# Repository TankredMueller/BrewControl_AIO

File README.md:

# BrewControl_AIO
A top hat rail implementation of the world famous AiO brew control.

For further information on AiO brewControl, see http://hobbybrauer.de/forum/wiki/doku.php/brauen_mit_arduino_all_in_one_aio

This project consists of the following parts:
- A PCB design suitable to be integrated in a top hat rail case
  -> for a preconfigured shopping cart, please use this link: https://www.reichelt.de/my/1339621
- A wiring plan (see https://github.com/TankredMueller/BrewControl_AIO/blob/master/AIO_project_wiring_plan.pdf)

Please note that this project is still in early beta status! You are welcome to build it, but don´t take it personally if something goes wrong. I will assume no responsibility for any use of this project.

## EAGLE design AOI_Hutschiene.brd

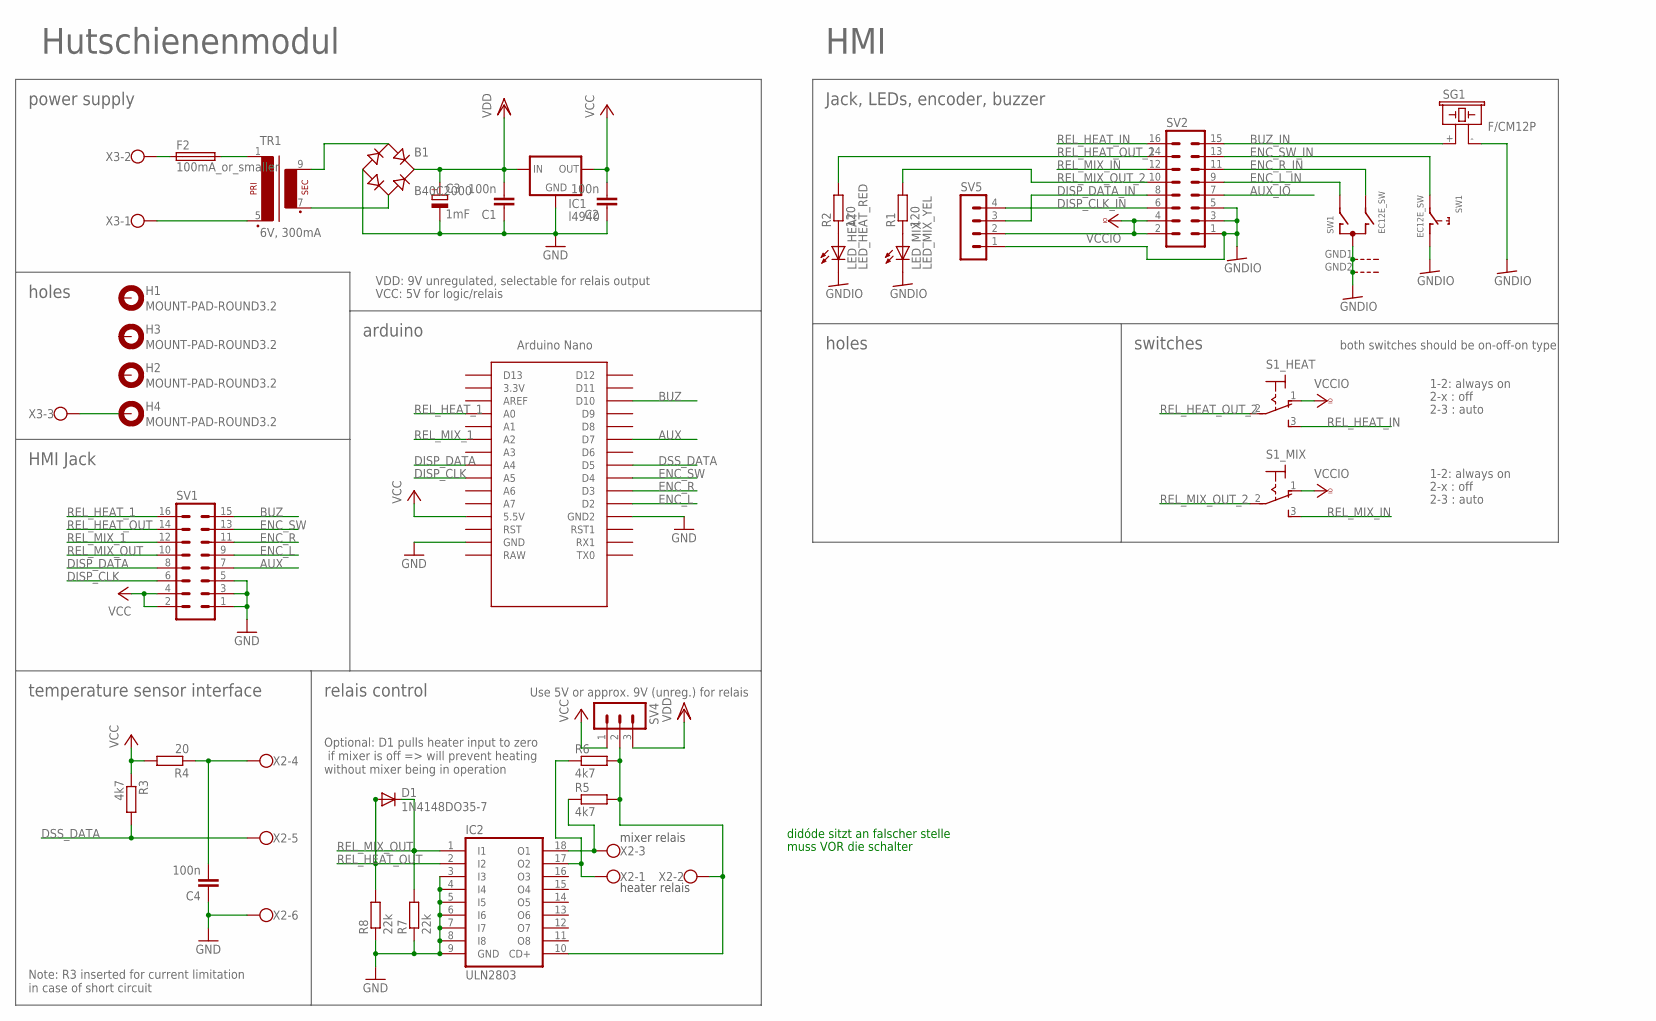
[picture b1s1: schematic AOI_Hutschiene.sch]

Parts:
B1: B40C2000; RB1A
C1, C2, C4: 100n; C025_050-025X075
C3: 1mF; E5-13
D1: 1N4148DO35-7; DO35-7
F2: 100mA_or_smaller; SH22,5
H1, H2, H3, H4: MOUNT-PAD-ROUND3.2; 3,2-PAD
IC1: l4940; 78XXS
IC2: ULN2803; DIL18
LED_HEAT: LED_HEAT_RED; LED5MM
LED_MIX: LED_MIX_YEL; LED5MM
R1, R2: 120; 0207/10
R3: 4k7; 0207/10
R4: 20; 0207/10
R5, R6: 4k7; 0207/2V
R7, R8: 22k; 0207/10
S1_HEAT, S1_MIX: M9040P
SG1: F/CM12P
SV1, SV2: ML16
SV4: MA03-1
SV5: MA04-1
SW1: EC12E_SW; ALPS_EC12E_SW
TR1: 6V, 300mA; EI30-1
U$1: ArdNano_with_socket; NANO
X2: W237-6
X3: W237-103

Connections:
AUX: SV1.7, U$1.D7
AUX_IO: SV2.7
BUZ: SV1.15, U$1.D10
BUZ_IN: SG1.+ (1), SV2.15
DISP_CLK: SV1.6, U$1.A5
DISP_CLK_IN: SV2.6, SV5.4
DISP_DATA: SV1.8, U$1.A4
DISP_DATA_IN: SV2.8, SV5.3
DSS_DATA: R3.2, U$1.D5, X2.5
ENC_L: SV1.9, U$1.D2
ENC_L_IN: SV2.9, SW1.A
ENC_R: SV1.11, U$1.D3
ENC_R_IN: SV2.11, SW1.B
ENC_SW: SV1.13, U$1.D4
ENC_SW_IN: SV2.13, SW1.E (2)
GND: B1.-, C1.1, C2.1, C3.-, C4.1, IC1.GND, IC2.3 (I3), IC2.4 (I4), IC2.5 (I5), IC2.6 (I6), IC2.7 (I7), IC2.8 (I8), IC2.9 (GND), R7.1, R8.1, SV1.1, SV1.3, SV1.5, U$1.GND, U$1.GND1 (GND2), X2.6
GNDIO: LED_HEAT.K (C), LED_MIX.K (C), SG1.- (2), SV2.1, SV2.3, SV2.5, SV5.1, SW1.C, SW1.D (1), SW1.GND1 (G), SW1.GND2 (G)
unnamed: IC2.10 (CD+), R5.2, R6.2, SV4.2, X2.2
unnamed: IC2.18 (O1), R5.1, X2.3
unnamed: IC2.17 (O2), R6.1, X2.1
unnamed: LED_HEAT.A, R2.1
unnamed: LED_MIX.A, R1.1
unnamed: F2.2, TR1.1
unnamed: F2.1, X3.2
unnamed: TR1.5 (P2), X3.1
unnamed: B1.AC1, TR1.9 (S4)
unnamed: B1.AC2, TR1.7 (S3)
unnamed: C4.2, R4.1, X2.4
unnamed: H4.B3,2, X3.3
REL_HEAT_1: SV1.16, U$1.A0
REL_HEAT_IN: S1_HEAT.3 (S), SV2.16
REL_HEAT_OUT: D1.A, IC2.2 (I2), R8.2, SV1.14
REL_HEAT_OUT_2: R2.2, S1_HEAT.2, SV2.14
REL_MIX_1: SV1.12, U$1.A2
REL_MIX_IN: S1_MIX.3 (S), SV2.12
REL_MIX_OUT: D1.C, IC2.1 (I1), R7.2, SV1.10
REL_MIX_OUT_2: R1.2, S1_MIX.2, SV2.10
VCC: C2.2, IC1.OUT, R3.1, R4.2, SV1.2, SV1.4, SV4.1, U$1.5V (5.5V)
VCCIO: S1_HEAT.1 (O), S1_MIX.1 (O), SV2.2, SV2.4, SV5.2
VDD: B1.+, C1.2, C3.+, IC1.IN, SV4.3

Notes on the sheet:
heater relais
mixer relais
Use 5V or approx. 9V (unreg.) for relais
power supply
arduino
Hutschienenmodul
HMI
holes
HMI Jack
Jack, LEDs, encoder, buzzer
switches
relais control
temperature sensor interface
VDD: 9V unregulated, selectable for relais output
VCC: 5V for logic/relais
Note: R3 inserted for current limitation in case of short circuit
1-2: always on
2-x : off
2-3 : auto
both switches should be on-off-on type
Optional: D1 pulls heater input to zero if mixer is off => will prevent heating without mixer being in operation
didóde sitzt an falscher stelle
muss VOR die schalter

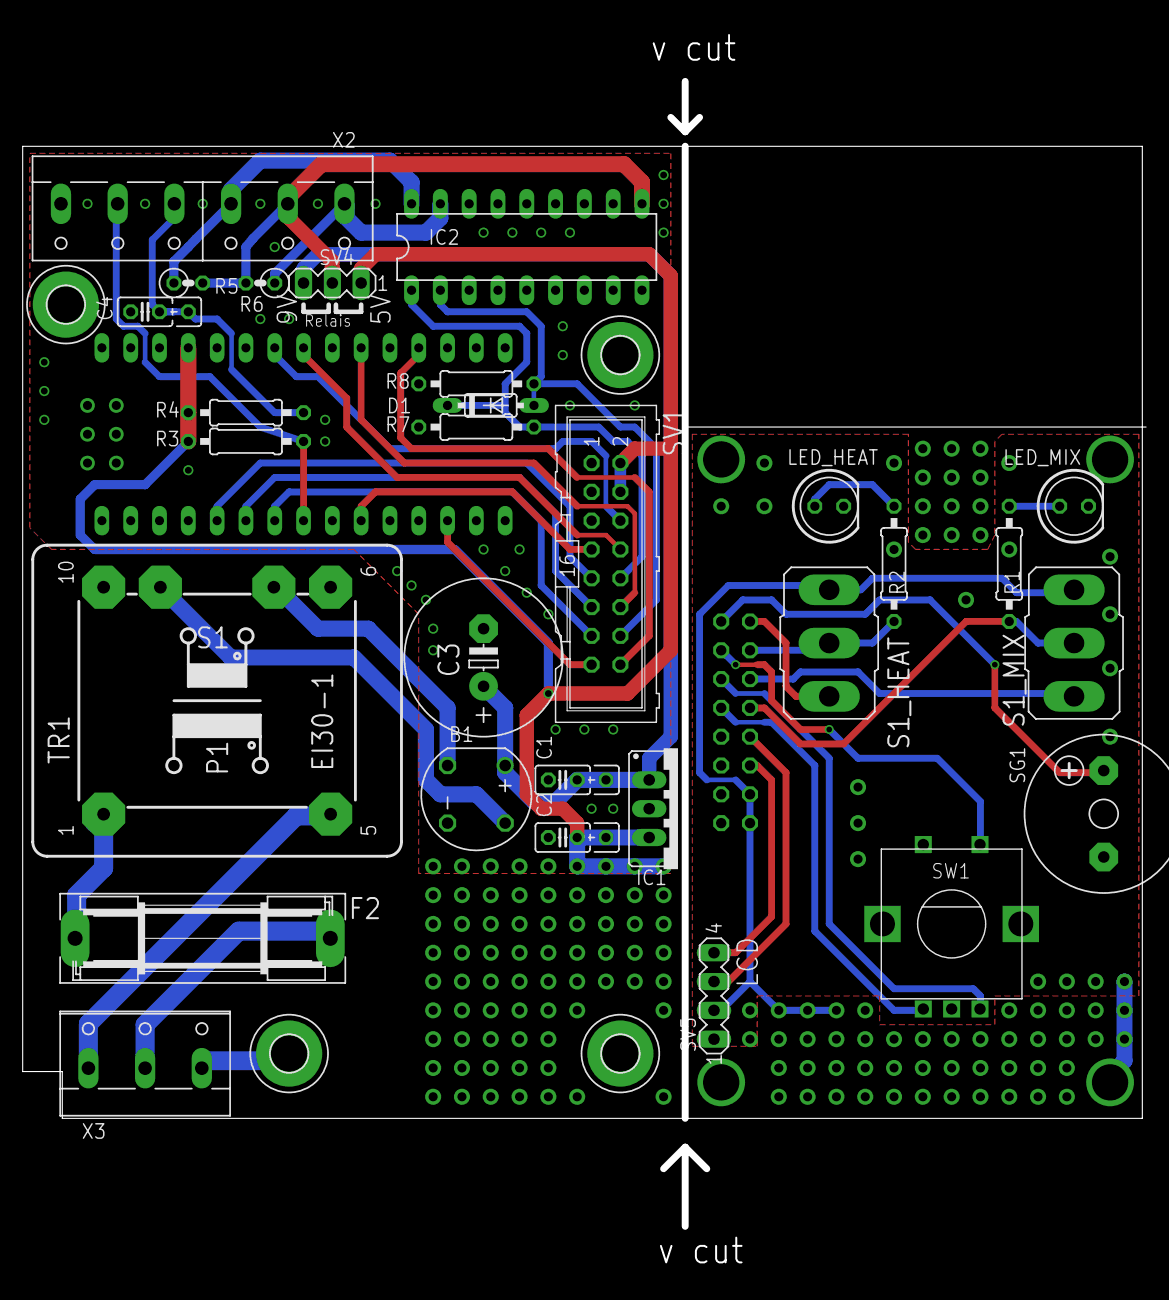
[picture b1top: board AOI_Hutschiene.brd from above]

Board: 2 copper layers, 98.5 x 110.0 mm, 35 parts (1 on the bottom side), 39 nets.

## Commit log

2017-04-17 :octocat: Added .gitattributes & .gitignore files
2017-04-17 Initial upload of board file and schematic
    Initial upload of board file and schematic
2017-04-17 added wiring plan
2017-07-04 updated design
2017-07-04 added schematic and component mounting scheme
2018-04-04 Bugfixes to schematic and board (D1, R3/R4)
    - D1: Wrong position. Declared as "dont use"
    - R3/R4: Wrong silk screen position in PCB. Fixed by interchanging component names in schematic
